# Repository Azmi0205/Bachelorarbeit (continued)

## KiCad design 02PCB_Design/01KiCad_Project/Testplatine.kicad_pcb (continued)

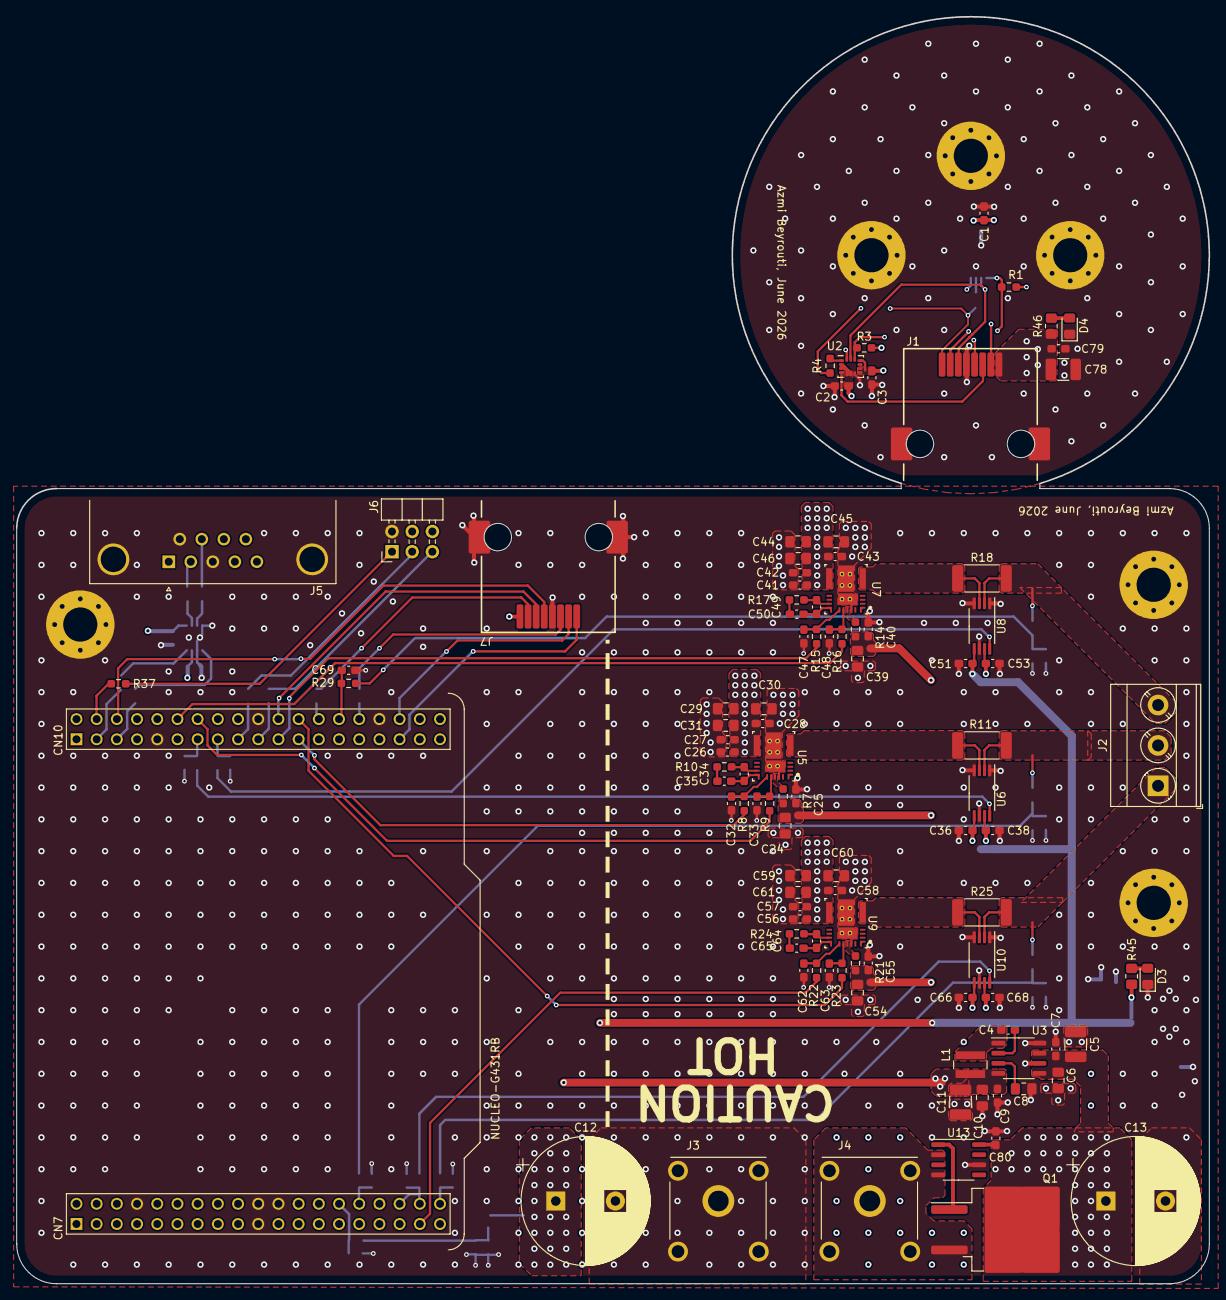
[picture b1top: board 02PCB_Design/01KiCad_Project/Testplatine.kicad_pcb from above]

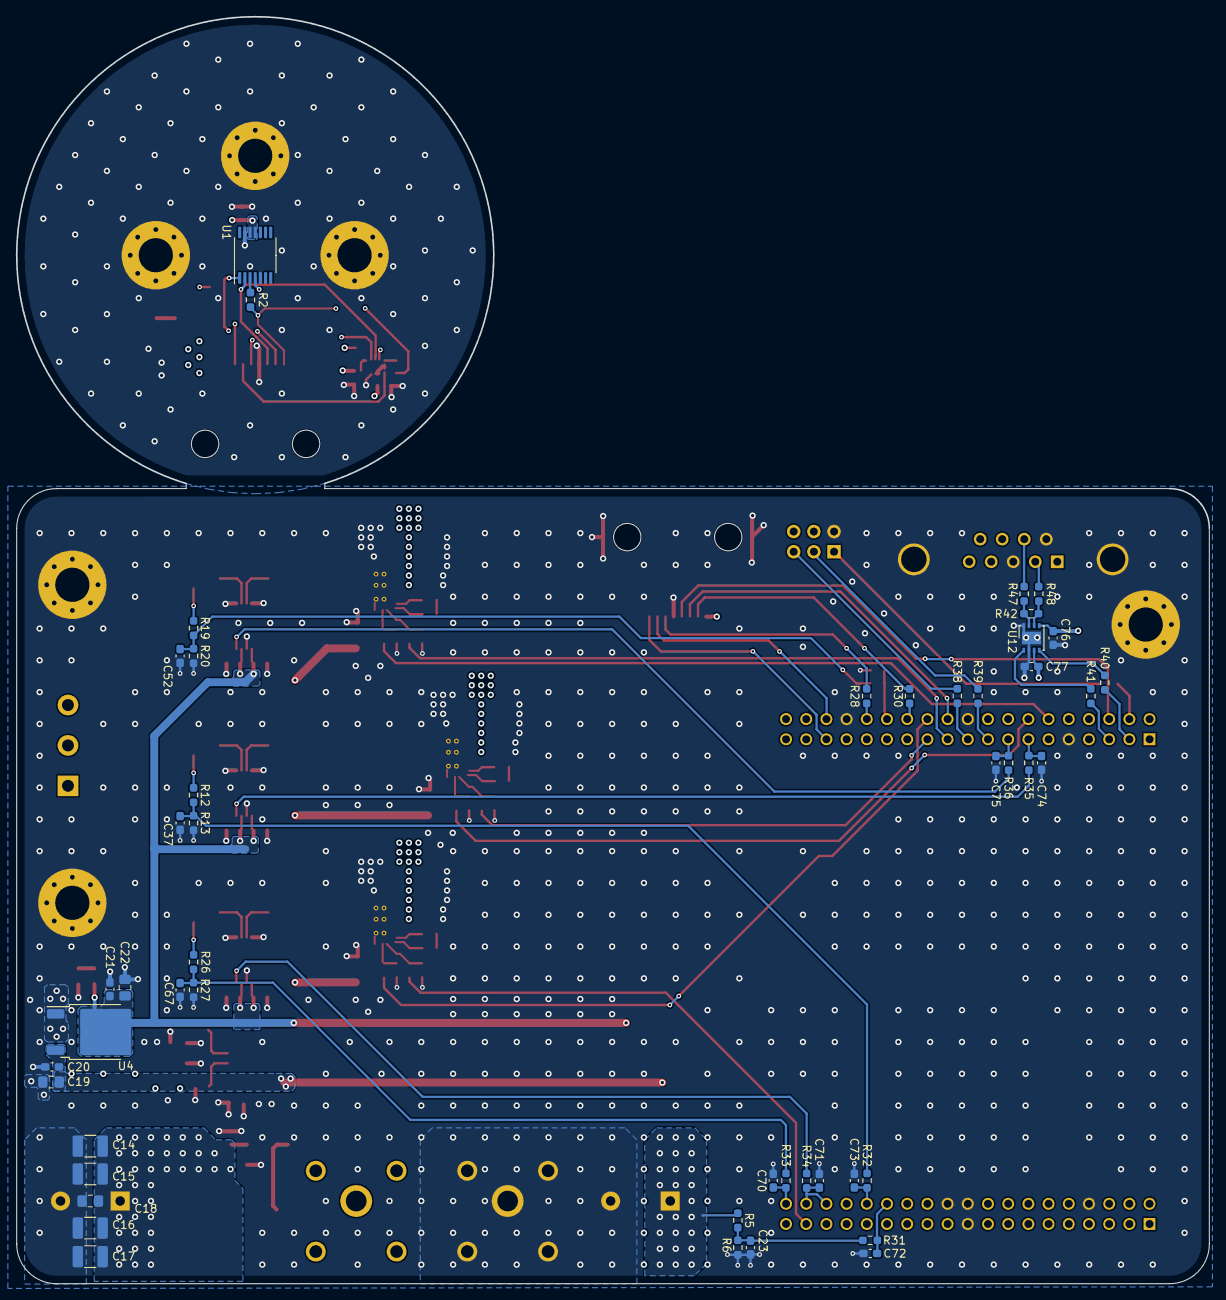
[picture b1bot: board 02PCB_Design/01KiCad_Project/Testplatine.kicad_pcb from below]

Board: 4 copper layers, 150.0 x 159.3 mm, 156 parts (48 on the bottom side), 87 nets.

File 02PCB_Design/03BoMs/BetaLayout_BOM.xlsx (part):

Part | Value | Device | Package | Description | Description2 | Qty | Place_YES/NO | Provided_by_customer_YES/NO | Distributor | Ordernumber | Remarks_Customer
U9,U7,U5 | LMG2100R044RARR | LMG2100R044RARR | VQFN-FCRLF-16 | 100-V 4.4-mΩ half-bridge GaN FET with integrated driver and protection |  | 3 | YES | NO | Mouser | 595-LMG2100R044RARR
C78,C5,C17,C14,C15,C16 | 10uF | GRM32EC72A106KE05L | C_1210 | Murata, GRM, Oberfläche Keramik-Vielschichtkondensator Keramik, 10 μF 10 % / 10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 |  | 6 | YES | NO | RS Components | 247-8166
C10,C8,C31,C30,C60,C45,C44,C61,C59,C46,C29,C6 | 1uF | CGA4J3X7S2A105K125AE | C_0805 | TDK, CGA, Oberfläche Keramik-Vielschichtkondensator X7S, 1 μF ±10 % / 100V dc, 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 |  | 12 | YES | NO | RS Components | 915-5263
J7,J1 | Wurth-634008 | 634008149821 | Wurth_634008_RJ45 | Buchse Cat.5 RJ45-Steckverbinder, 1-Port 8-polig Messing vernickelt Oberfläche 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 |  | 2 | YES | NO | RS Components | 162-2309
C49,C35,C36,C53,C50,C7,C4,C65,C1,C55,C2,C3,C79,C68,C38,C51,C34,C40,C66,C9,C25,C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 | 100nF | VJ0603Y104KXBCW1BC | C_0603 | Vishay, W1BC, Oberfläche Keramik-Vielschichtkondensator X7R, 0.1 μF ±0.1 % / 10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 |  | 26 | YES | NO | RS Components | 272-7888P
R11,R25,R18 | 3m | BVT-I-R003-1.0 | R_2512 | Isabellenhütte BVT, AEC-Q200 Zeranin SMD-Widerstand 3 mΩ ±1 % / 3 W 50 ppm/K |  | 3 | YES | NO | RS Components | 193-0036
R14,R21,R10,R17,R24,R7 | 10R | CRCW060310R0FKEA | R_0603 | Vishay CRCW, AEC-Q200 Dickschicht SMD-Widerstand 10 Ω ±1 % / 0.1 W -100 ppm/°C,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 |  | 6 | YES | NO | RS Components | 678-9695
D4,D3 | LED | LS R976-NR-1 | LED_0805 | ams OSRAM CHIP LED 0805 Oberfläche LED Rot 2 V, 160 °, 2-Pin |  | 2 | YES | NO | RS Components | 497-4804
C33,C47,C63,C62,C48,C32 | 47pF | C0603C470J5GACTU | C_0603 | KEMET, C, Oberfläche Keramik-Vielschichtkondensator C0G, 47 pF ±5 % / 50V dc |  | 6 | YES | NO | RS Components | 264-4517
U10,U8,U6 | INA240A1PW | INA240A1PWR | TSSOP-8_4.4x3mm_P0.65mm | Texas Instruments Stromsensor 25 μV 1.8 mA TSSOP, 8-Pin Oberfläche |  | 3 | YES | NO | RS Components | 226-4772
C57,C43,C42,C58,C26,C41,C27,C28,C56 | 220nF | GCM188R71H224KA64J | C_0603 | Murata, GCM, Oberfläche Keramik-Vielschichtkondensator X7R, 220 nF ±10 % / 50V 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 |  | 9 | YES | NO | RS Components | 247-7879P
R16,R22,R15,R29,R9,R8,R23,R33,R35,R36,R32,R34,R31 | 20R | RS Best.-Nr.: 243-0578P | R_0603 | RS PRO RSTN Dünnschicht Widerstand 22 Ω 0.5 % / 0.15 W ±50 to 100 ppm/°C |  | 13 | YES | NO | RS Components | 243-0578P | 20Ω not available; 22Ω as alternative
R46,R45 | 2.2k | RS Best.-Nr.: 243-0666 | R_0805 | RS PRO RSTN Dünnschicht Widerstand 2.2 kΩ 0.1 % / 0.4 W ±50 to 100 ppm/°C |  | 2 | YES | NO | RS Components | 243-0666
Q1 | IPB020N10N5 | IPB020N10N5ATMA1 | TO-263-2 | Infineon IPB020N10N5 Typ N-Kanal, Oberfläche MOSFET Erweiterung 100 V / 176 A 3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 |  | 1 | YES | NO | RS Components | 171-1955
R1,R3,R19,R12,R5,R26 | 100k | RT0603BRD07100KL | R_0603 | Yageo RT Dünnschicht SMD-Widerstand 100 kΩ ±0.1 % / 0.1 W 25 ppm/°C |  | 6 | YES | NO | RS Components | 199-1385
U2 | ISM330BXTR | ISM330BXTR | LGA-14_3x2.5mm_P0.5mm_LayoutBorder3x4y | STMicroelectronics Näherungsschalter 6-Achsen Oberfläche 1.71 V 3.6V 2.8 kHz Tr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 |  | 1 | YES | NO | RS Components | 151-685
R37,R4,R39,R38,R2,R28,R30 | 33R | CRCW060333R0FKEAHP | R_0603 | Vishay CRCW, AEC-Q200 Dickschicht SMD-Widerstand 33 Ω ±1 % Oberfläche / 0.25 W 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 |  | 7 | YES | NO | RS Components | 820-6837
C69,C75,C73,C70,C72,C71,C74 | 2.2nF | CGA3E2C0G1H222J080AA | C_0603 | TDK, CGA, Oberfläche Keramik-Vielschichtkondensator C0G, 2.2 nF ±5 % / 50V dc |  | 7 | YES | NO | RS Components | 915-5705P
C24,C54,C39 | 2.2uF | C2012X7R1H225K125AC | C_0805 | TDK, C, Oberfläche Keramik-Vielschichtkondensator X7R, 2.2 μF ±10 % / 50V dc |  | 3 | YES | NO | RS Components | 788-3048P
C80 | 47nF | C0603C473K1RACTU | C_0603 | KEMET, C, Oberfläche Keramik-Vielschichtkondensator X7R, 47 nF ±10 % / 100V dc |  | 1 | YES | NO | RS Components | 801-5384
J5 | RS PRO 528 D-Sub 2.77mm | RS Best.-Nr.: 239-5855 | DSUB-9_Female_Horizontal_P2.77x2.84mm_EdgePinOffset4.94mm_Housed_MountingHolesO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 | RS PRO D-Sub-Steckverbinder D gewinkelt, 9-polig 2.77 mm Raster, Durchsteckmont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 |  | 1 | YES | NO | RS Components | 239-5855
C12,C13 | 470uF | ECA2AHG471 | CP_Radial_D16.0mm | Panasonic NHG Radial, Durchsteckmontage Kondensator 470 μF Radiale Anschlussfah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 |  | 2 | YES | NO | RS Components | 365-4543P
C11 | 47uF | GRM32EC81C476KE15L | C_1210 | Murata, GRM, Oberfläche Keramik-Vielschichtkondensator X6S, 47 μF ±10 % / 16V dc |  | 1 | YES | NO | RS Components | 846-7369
L1 | 22uH | 74438356220 | L_Wuerth_MAPI-4020 | Wurth Elektronik WE-MAPI SMT Power-Induktivität mit Abschirmung, 22 μH 1.85 A A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 |  | 1 | YES | NO | RS Components | 258-5689
U3 | L6982C50DR | L6982C50DR | SO-8_3.9x4.9mm_P1.27mm | STMicroelectronics Spannungsregler 38V, 8-Pin |  | 1 | YES | NO | RS Components | 261-4749P
J2 | Wurth Elektronic 2365 Printklemme | 691236510003 | Wurth Elektronik 2365 Printklemme | Wurth Elektronik 2365 Printklemme Horizontal, Durchsteckmontage, 3-polig / 1-re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 |  | 1 | YES | NO | RS Components | 191-0204
U13 | LTC4359 | LTC4359IS8#PBF | SO-8_3.9x4.9mm_P1.27mm | Power Management Specialised - PMIC Ideal Diode Cntr w/ Reverse In Protectopm |  | 1 | YES | NO | Mouser | 584-LTC4359IS8#PBF
U1 | AS5047P-ATSM | AS5047P-ATSM | TSSOP-14_4.4x5mm_P0.65mm | ams OSRAM 14-Bit-Magnetischer Drehpositionssensor auf der Achse 1-Achsen Oberfl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 |  | 1 | YES | NO | RS Components | 200-9464
C67,C52,C37,C23 | 33nF | C0603C333K5RACTU | C_0603 | KEMET, C, Oberfläche Keramik-Vielschichtkondensator X7R, 33 nF ±10 % / 50V dc |  | 4 | YES | NO | RS Components | 147-869
R41,R48,R40,R47 | 0R | MCR03SEQPJ000 | R_0603 | ROHM MCRS Series, AEC-Q200 Dickschicht Widerstand 0 Ω ±5 % Oberfläche / 0.125 W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 |  | 4 | YES | NO | RS Components | 780-542
C22,C18,C19 | 4.7uF | C0805C475K3RACAUTO | C_0805 | KEMET, VW 80828 Keramik-Vielschichtkondensator X7R, 4.7 μF 10 % / 50V |  | 3 | YES | NO | RS Components | 188-2142P
U4 | AP2114D | AP2114D-3.3TRG1 | TO-252-2 | DiodesZetex Regler, Rauscharmer LDO 5 1 A TO-252 3.3V |  | 1 | YES | NO | RS Components | 828-3515
R27,R6,R20,R13 | 4.22k | CRCW06034K22FKEA | R_0603 | Vishay CRCW, AEC-Q200 Dickschicht SMD-Widerstand 4.22 kΩ ±1 % / 0.1 W -100 ppm/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 |  | 4 | YES | NO | RS Components | 679-0465
U12 | MCP2562FD-E/MF | MCP2562FD-E/MF | DFN-8-1EP_3x3mm_P0.65mm_EP1.55x2.4mm | Microchip CAN-Transceiver, 8 Mbit/s 1 Transceiver Standby 70 mA |  | 1 | YES | NO | RS Components | 824-3135
R42 | 120R | RN73R1JTTD1200B25 | R_0603 | KOA RN73R, AEC-Q200 Metallschicht SMD-Widerstand 120 Ω ±0.1 % / 0.1 W ±25 ppm/°C |  | 1 | YES | NO | RS Components | 253-3100
U11 | NUCLEO-G431RB | ESQ-119-24-T-D | 2x19 Leiterplattenbuchse; 2.54mm Raster | Samtec ESQ Leiterplattenbuchse Gerade Durchsteckmontage 38-polig / 2-reihig, Ra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 |  | 2 | NO | NO | RS Components | 196-9830 | Two articles are needed to fill a single footprint; Please Also Order
J4,J3 | RS Pro 304-02-818 | RS Best.-Nr.: 187-3802 | S16N-PC 4mm Shrouded socket | RS PRO 4 mm Buchse Schwarz, Rot Buchse für Laborstecker, Kontakt Gold, 1kV 24A 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 |  | 1 | NO | NO | RS Components | 187-3802 | A single article fills two footprints; Please Also Order
J6 | Conn_02x03_Pin | TSW-106-08-L-D-RA | PinHeader_2x03_P2.54mm_Horizontal | Samtec TSW Stiftleiste gewinkelt, 12-polig / 2-reihig, Raster 2.54 mm Raster Du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 |  | 1 | NO | NO | RS Components | 767-0934 | Article has 12 poles; Cut to fit; Please Also Order
- | 9471LE (1/2 IN X 60 YD) | - | - | hermal Interface Products Adhesive Thermal Transfer Tape, Clear, 1/2 in x 60 yd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 |  | 1 | NO | NO | Mouser | 517-9471LE-1/2IN | Non-electrical item; Please Also Order
- | Fischer Elektronik Kühlkörper L | ICK S 40x40x20 | - | Fischer Elektronik Kühlkörper für Universelle quadratische Alu, 40 mm x 40mm x 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 |  | 1 | NO | NO | RS Components | 674-4835 | Non-electrical item; Please Also Order
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
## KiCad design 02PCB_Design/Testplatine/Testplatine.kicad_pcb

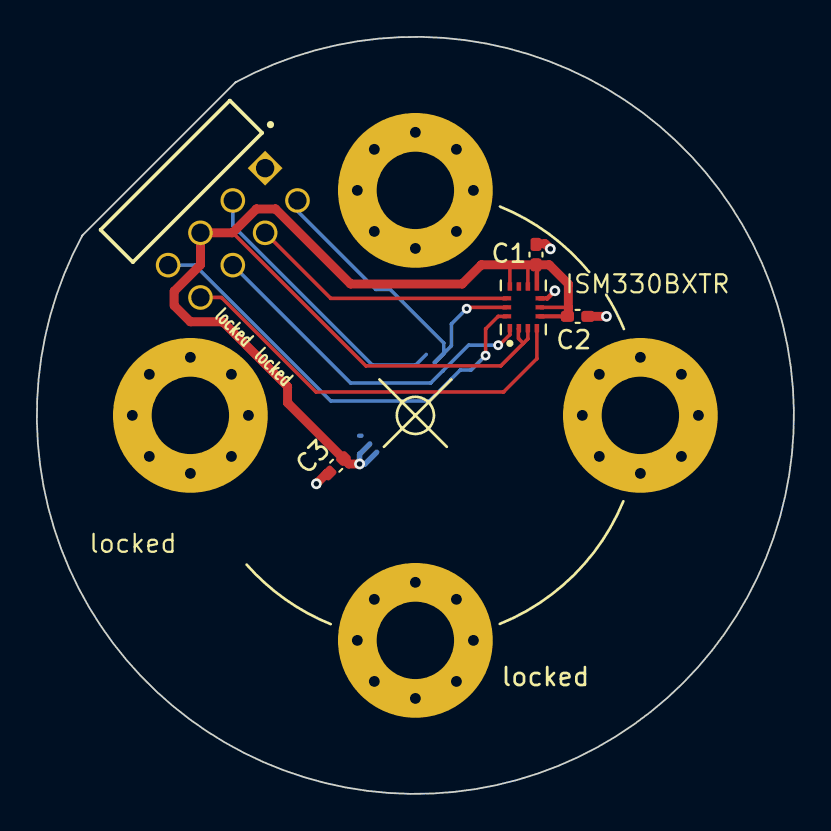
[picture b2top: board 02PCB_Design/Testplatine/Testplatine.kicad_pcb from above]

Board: 2 copper layers, 42.1 x 42.1 mm, 10 parts (1 on the bottom side), 8 nets.

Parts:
C1, C2, C3: 100nF; C_0402_1005Metric_Pad0.74x0.62mm_HandSolder
H1, H2, H3, H4: MountingHole; MountingHole_4.3mm_M4_Pad_Via
J2: MTSW-104-22-L-D-265-RA; SAMTEC_MTSW-104-22-L-D-265-RA
U1: ISM330BXTR; XDCR_ISM330BXTR
U2: AS5047P-ATSM; SOP65P640X120-14N

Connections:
/SensorSheet/3.3SPI: C1.1, C2.1, C3.1, J2.05, U1.2 (TDMOUT), U1.3 (BCLK), U1.5 (VDDIO), U1.6 (AH1/QVAR1), U1.8 (VDD), U1.9 (AH2/QVAR2), U1.11 (WCLK), U2.11 (VDD), U2.12 (VDD3V3)
/SensorSheet/ENC_CS: J2.03, U2.1 (CSN)
/SensorSheet/IMU_CS: J2.04, U1.12 (CS)
/SensorSheet/IMU_INT1: J2.08, U1.4 (INT1)
/SensorSheet/SPI_MISO: J2.06, U1.1 (SDO/TA0), U2.3 (MISO)
/SensorSheet/SPI_MOSI: J2.07, U1.14 (SDA), U2.4 (MOSI)
/SensorSheet/SPI_SCLK: J2.02, U1.13 (SCL), U2.2 (CLK)
GND: C1.2, C2.2, C3.2, J2.01, U1.7 (GND), U2.5 (TEST), U2.13 (GND)

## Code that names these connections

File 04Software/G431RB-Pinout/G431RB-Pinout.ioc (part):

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Mcu.Name=STM32G431R(6-8-B)Tx
Mcu.Package=LQFP64
Mcu.UserName=STM32G431RBTx
PA0.GPIOParameters=GPIO_Label
PA0.GPIO_Label=VOLTAGE_BUS
PA0.Mode=IN1-Single-Ended
PA0.Signal=ADC1_IN1
PA1.GPIOParameters=GPIO_Label
PA1.GPIO_Label=CURRENT_U
PA1.Mode=IN2-Single-Ended
PA1.Signal=ADC2_IN2
PA10.Mode=Full_Duplex_Master
PA10.Signal=SPI2_MISO
PA11.Mode=PWM Generation1 CH1 CH1N
PA11.Signal=TIM1_CH1N
PA12.Mode=PWM Generation2 CH2 CH2N
PA12.Signal=TIM1_CH2N
PA13.GPIOParameters=GPIO_Label
PA13.GPIO_Label=T_SWDIO
PA13.Mode=Serial_Wire
PA13.Signal=SYS_JTMS-SWDIO
PA14.GPIOParameters=GPIO_Label
PA14.GPIO_Label=T_SWCLK
PA14.Mode=Serial_Wire
PA14.Signal=SYS_JTCK-SWCLK
PA15.Mode=I2C
PA15.Signal=I2C1_SCL
PA2.GPIOParameters=GPIO_Label
PA2.GPIO_Label=LPUART1_TX [STLINKV3E_VCP_RX]
PA2.Mode=Asynchronous
PA2.Signal=LPUART1_TX
PA3.GPIOParameters=GPIO_Label
PA3.GPIO_Label=LPUART1_RX [STLINKV3E_VCP_TX]
PA3.Mode=Asynchronous
PA3.Signal=LPUART1_RX
PA4.GPIOParameters=GPIO_Label
PA4.GPIO_Label=EN_3.3V
PA4.Signal=GPIO_Output
PA5.GPIOParameters=GPIO_Label
PA5.GPIO_Label=LD2 [green]
PA5.Signal=GPIO_Output
PA6.GPIOParameters=GPIO_Label
PA6.GPIO_Label=CURRENT_V
PA6.Mode=IN3-Single-Ended
PA6.Signal=ADC2_IN3
PA7.GPIOParameters=GPIO_Label
PA7.GPIO_Label=CURRENT_W
PA7.Mode=IN4-Single-Ended
PA7.Signal=ADC2_IN4
PA8.Signal=S_TIM1_CH1
PA9.Signal=S_TIM1_CH2
PB0.Mode=INP
PB0.Signal=COMP4_INP
PB1.Mode=PWM Generation3 CH3 CH3N
PB1.Signal=TIM1_CH3N
PB13.Mode=Full_Duplex_Master
PB13.Signal=SPI2_SCK
PB14.GPIOParameters=GPIO_Label
PB14.GPIO_Label=VOLTAGE_U
PB14.Mode=IN5-Single-Ended
PB14.Signal=ADC1_IN5
PB15.Mode=Full_Duplex_Master
PB15.Signal=SPI2_MOSI
PB2.GPIOParameters=GPIO_Label
PB2.GPIO_Label=IMU_INT1
PB2.Signal=GPXTI2
PB3.GPIOParameters=GPIO_Label
PB3.GPIO_Label=T_SWO
PB3.Signal=SYS_JTDO-SWO
PB6.Signal=S_TIM8_ETR
PB7.Mode=I2C
PB7.Signal=I2C1_SDA
PB8-BOOT0.Mode=FDCAN_Activate
PB8-BOOT0.Signal=FDCAN1_RX
PB9.Mode=FDCAN_Activate
PB9.Signal=FDCAN1_TX
PC0.GPIOParameters=GPIO_Label
PC0.GPIO_Label=VOLTAGE_V
PC0.Mode=IN6-Single-Ended
PC0.Signal=ADC1_IN6
PC1.GPIOParameters=GPIO_Label
PC1.GPIO_Label=VOLTAGE_W
PC1.Mode=IN7-Single-Ended
PC1.Signal=ADC1_IN7
PC13.GPIOParameters=GPIO_Label
PC13.GPIO_Label=B1 [blue push button]
PC13.Signal=GPXTI13
PC14-OSC32_IN.Mode=LSE-External-Oscillator
PC14-OSC32_IN.Signal=RCC_OSC32_IN
PC15-OSC32_OUT.Mode=LSE-External-Oscillator
PC15-OSC32_OUT.Signal=RCC_OSC32_OUT
PC2.Signal=S_TIM1_CH3
PC4.Signal=GPIO_Output
PC5.GPIOParameters=GPIO_Label
PC5.GPIO_Label=IMU_CS
PC5.Signal=GPIO_Output
PC6.Signal=S_TIM8_CH1
PC7.Signal=S_TIM8_CH2
PC8.Mode=I2C
PC8.Signal=I2C3_SCL
PC9.Mode=I2C
PC9.Signal=I2C3_SDA
PF0-OSC_IN.Mode=HSE-External-Oscillator
PF0-OSC_IN.Signal=RCC_OSC_IN
PF1-OSC_OUT.Mode=HSE-External-Oscillator
PF1-OSC_OUT.Signal=RCC_OSC_OUT
RCC.HSE_VALUE=24000000
RCC.SYSCLKFreq_VALUE=170000000
RCC.SYSCLKSource=RCC_SYSCLKSOURCE_PLLCLK
board=NUCLEO-G431RB
boardIOC=true

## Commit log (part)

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2026-01-21 restructure
2026-01-22 added CAN + minor changes
2026-01-26 cleanup
2026-01-28 besprechung
2026-05-01 Added Footprints for Passive components
2026-05-20 Layout progress
2026-05-22 routed signals
2026-05-25 Design 1.0 Finished
